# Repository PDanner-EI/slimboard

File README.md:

# Slimboard
Slim profile, split keyboard. Inspired by Corne(https://github.com/foostan/crkbd).

## Features:
- Split keyboard
- Slim profile for easy portability
- Bluetooth connectivity
- Key Layout fitted to own hand

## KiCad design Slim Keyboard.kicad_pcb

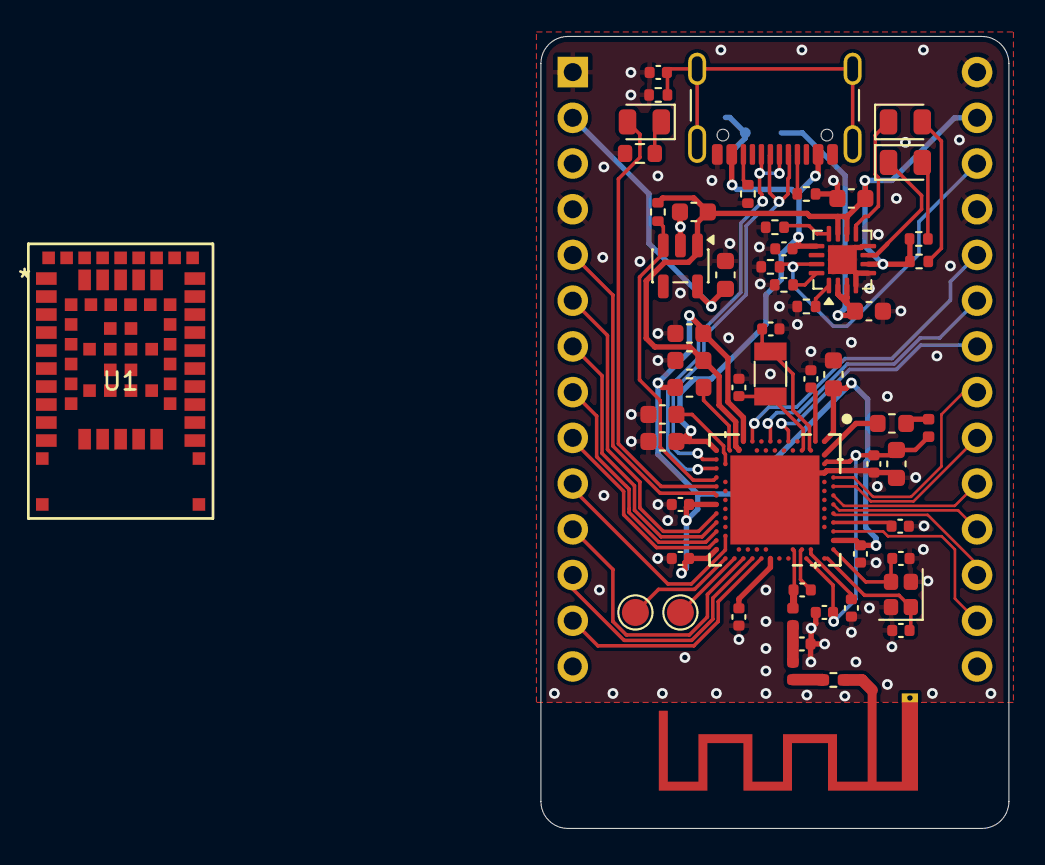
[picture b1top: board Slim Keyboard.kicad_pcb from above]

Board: 2 copper layers, 26.0 x 44.0 mm, 59 parts (1 on the bottom side), 61 nets.

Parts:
AE1: Antenna_Shield; 2.4GHz F Antenna
C1, C2, C6, C18: 100nF; C_0402_1005Metric
C3, C4, C11, C12: 12pF; C_0402_1005Metric
C5, C19, C20, C21, C23, C24, C25: 4.7uF; C_0603_1608Metric
C7, C8: 1uF; C_0603_1608Metric
C9: 47nF; C_0402_1005Metric
C10, C14: N.C.; C_0402_1005Metric
C13: 100pF; C_0402_1005Metric
C15: 1pF; C_0402_1005Metric
C16: 1.2pF; C_0402_1005Metric
C17: 820pF; C_0402_1005Metric
C22: 1uF; C_0402_1005Metric
C26: 10uF; C_0603_1608Metric
C27: 4.7nF; C_0402_1005Metric
D1: LTST-C170KFKT; LED_0805_2012Metric
D2: LTST-C170KGKT; LED_0805_2012Metric
D3: IN-S85AT5B; LED_0805_2012Metric
J1: USB_C_Receptacle_USB2.0_16P; USB_C_Receptacle_GCT_USB4105-xx-A_16P_TopMnt_Horizontal
J2: SWD; TestPoint_Pad_D1.5mm
J3: SWC; TestPoint_Pad_D1.5mm
J5: S2B-PH-SM4-TB; JST_S2B-PH-SM4-TB
J7: NRF52840_module
L1, L5: 10uH; L_0603_1608Metric
L2: 15nH; L_0402_1005Metric
L3: 4.7nH; L_0402_1005Metric
L4: 2.2nH; L_0402_1005Metric
R1: 0R; R_0402_1005Metric_Pad0.72x0.64mm_HandSolder
R2, R12: 1M; R_0402_1005Metric
R3: 10k; R_0402_1005Metric
R4, R5: 1k; R_0402_1005Metric
R6: 10M; R_0402_1005Metric
R7, R8: 5.1k; R_0402_1005Metric
R9: 1k; R_0603_1608Metric
R10: 3.1k; R_0402_1005Metric
R11: 3.6k; R_0402_1005Metric
U1: NINA-B306-00B; NINA-B3x6_UBL
U1#2: NRF52840-QIAA-R; AQFN73_7X7_NOR
U2: BQ24075RGT; VQFN-16-1EP_3x3mm_P0.5mm_EP1.6x1.6mm
U3: XC6220B331MR; SOT-23-5
Y1: ECS-.327-9-34B-TR; Crystal_SMD_3215-2Pin_3.2x1.5mm
Y2: XRCGB32M000F1S2KR0; Crystal_SMD_2016-4Pin_2.0x1.6mm

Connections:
BLED: D3.2 (A), U1.44 (GPIO_44), U1#2.AD10 (P0.15)
D0: J7.3 (D0_P0.08), U1.1 (GPIO_1)
D1: J7.2 (D1_P0.06), U1.2 (GPIO_2)
D2: J7.6 (D2_P0.17), U1.3 (GPIO_3)
D3: J7.7 (D3_P0.20), U1.4 (GPIO_4)
D4: J7.8 (D4_P0.22), U1.5 (GPIO_5)
D5: J7.9 (D5_P0.24), U1.7 (GPIO_7)
D6: J7.10 (D6_P1.00), U1.16 (GPIO_16)
D7: J7.11 (D7_P0.11), U1.17 (GPIO_17)
D8: J7.12 (D8_P1.04), U1.18 (GPIO_18)
D9: J7.13 (D9_P1.06), U1.20 (GPIO_20)
D11: J7.14 (D11_P0.09), U1.21 (GPIO_21)
D14: J7.16 (D14_P1.11), U1.22 (GPIO_22)
D15: J7.17 (D15_P1.13), U1.23 (GPIO_23)
D16: J7.15 (D16_P0.10), U1.24 (GPIO_24)
D18: J7.18 (D18_P1.15), U1.25 (GPIO_25)
D19: J7.19 (D19_P0.02), U1.27 (GPIO_27)
D20: J7.20 (D20_P0.29), U1.34 (GPIO_34)
D+: J1.A6 (D+), J1.B6 (D+), U1.54 (USBG_DP), U1#2.AD6 (D+)
D-: J1.A7 (D-), J1.B7 (D-), U1.55 (USBG_DM), U1#2.AD4 (D-)
EXT_VCC: C25.1, U3.5 (VOUT)
GND: AE1.2 (Shield), C1.2, C2.2, C3.2, C4.2, C5.2, C6.1, C7.1, C8.1, C9.1, C10.2, C11.2, C12.2, C13.1, C14.1, C15.1, C16.1, C17.2, C18.1, C19.2, C20.2, C21.2, C22.1, C23.2, C24.2, C25.2, C26.1, C27.1, J1.A1 (GND), J1.A12 (GND), J1.B1 (GND), J1.B12 (GND), J5.2, J7.1 (GND), J7.4 (GND), J7.5 (GND), J7.24 (GND), R2.2, R3.2, R7.2, R8.2, R9.2, R10.2, R11.2, R12.1, U1.6 (GND), U1.12 (GND), U1.14 (GND), U1.26 (GND), U1.30 (GND), U1.53 (GND), U1.EAGP1 (GND), U1.EAGP2 (GND), U1.EAGP3 (GND), U1.EAGP4 (GND), U1.EGP1 (GND), U1.EGP2 (GND), U1.EGP3 (GND), U1.EGP4 (GND), U1.EGP5 (GND), U1.EGP6 (GND), U1.EGP7 (GND), U1.EGP8 (GND), U1.EGP9 (GND), U1.EGP10 (GND), U1.EGP11 (GND), U1.EGP12 (GND), U1#2.74 (VSS), U1#2.B7 (VSS), U1#2.F23 (VSS_PA), U2.4 (~CE), U2.5 (EN2), U2.8 (VSS), U2.17 (VSS), U3.2 (GND), Y2.2, Y2.4
unnamed: AE1.1 (A), R1.2
unnamed: C16.2, L3.2, L4.1
unnamed: D1.2 (A), R4.1
unnamed: D1.1 (K), U2.9 (~CHG)
unnamed: D2.2 (A), R5.1
unnamed: D2.1 (K), U2.7 (~PGOOD)
unnamed: D3.1 (K), R9.1
unnamed: J1.A5 (CC1), R7.1
unnamed: J1.B5 (CC2), R8.1
unnamed: C27.2, J1.S1 (SHIELD), R12.2
unnamed: L1.2, L2.1
unnamed: L4.2, R1.1
unnamed: C15.2, L3.1, U1#2.H23 (ANT)
unnamed: L1.1, U1#2.B3 (DCC)
unnamed: L5.1, U1#2.AB2 (DCCH)
unnamed: C2.1, U1#2.C1 (DEC1)
unnamed: C10.1, U1#2.A18 (DEC2)
unnamed: C13.2, U1#2.D23 (DEC3)
unnamed: C8.2, C9.2, C14.2, L2.2, U1#2.B5 (DEC4), U1#2.E24 (DEC6)
unnamed: C17.1, U1#2.N24 (DEC5)
unnamed: C5.1, U1#2.AC5 (DECUSB)
unnamed: C3.1, U1#2.D2 (P0.00/XL1), Y1.2
unnamed: C4.1, U1#2.F2 (P0.01/XL2), Y1.1
unnamed: C12.1, U1#2.B24 (XC1), Y2.1
unnamed: C11.1, U1#2.A23 (XC2), Y2.3
unnamed: R10.1, U2.12 (ILIM)
unnamed: R11.1, U2.16 (ISET)
unnamed: R3.1, U2.1 (TS)
POWER_PIN: R6.1, U1#2.AD8 (P0.13), U3.3 (CE)
RESET: J7.23 (RESET), U1.19 (RESET_N)
SWC: J3.1, U1.11 (SWDCLK), U1#2.AA24 (SWDCLK)
SWD: J2.1, U1.15 (SWDIO), U1#2.AC24 (SWDIO)
SYSOFF_SWITCH: J7.21 (D21_P0.31), R2.1, U2.15 (SYSOFF)
VBAT: C24.1, J5.1, U2.2 (BAT), U2.3 (BAT)
VBUS: C19.1, C22.2, J1.A4 (VBUS), J1.A9 (VBUS), J1.B4 (VBUS), J1.B9 (VBUS), U1.31 (VBUS), U1#2.AD2 (VBUS), U2.13 (IN)
VDD: U1.9 (VCC_IO), U1.10 (VCC)
VDDH: C20.1, C23.1, C26.2, R4.2, R5.2, R6.2, U1#2.Y2 (VDDH), U2.6 (EN1), U2.10 (OUT), U2.11 (OUT), U3.1 (VIN)
VDD_NRF: C1.1, C6.2, C7.2, C18.2, C21.1, L5.2, U1#2.A22 (VDD), U1#2.AD14 (VDD), U1#2.AD23 (VDD), U1#2.B1 (VDD), U1#2.W1 (VDD)
_GPIO: U1.35 (GPIO_35), U1.36 (GPIO_36), U1.37 (GPIO_37), U1.38 (GPIO_38), U1.39 (GPIO_39), U1.40 (GPIO_40), U1.41 (GPIO_41), U1.42 (GPIO_42), U1.43 (GPIO_43)

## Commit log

2026-02-20 Enhance README with features and link
    Added features section and improved project description.
2026-02-20 Initial commit; MCU designed after manufacturer specs
2026-02-20 Replaced 32MHz Crystal with 3-pin for added shielding
2026-02-20 Removed floating GND symbol
2026-02-20 Added 0 Ohm resistor before antenna for later VNA tuning
2026-02-20 Added proper Labels
2026-02-20 Added charging schematic
2026-02-20 Added external VCC schematic
2026-02-20 Added USB connection
2026-02-21 Update footprints
2026-02-21 Added ISET and JST to Battery
2026-02-21 Updated Footprints
2026-02-21 Added PCB Test Layout
2026-02-21 Adjusted PCB Test Layout
2026-02-25 Added test Antenna
2026-02-25 Added actual JST connector
2026-02-26 Adjusted Footprint sizes
2026-02-27 Started PCB design
2026-03-09 Changed Pinout
2026-03-09 Changed Module Pinout
2026-03-09 Connected GPIO
2026-03-09 Placed Components and started routing
2026-03-10 Routing
2026-03-10 Routing Done; DFM problems to solve
2026-03-14 DFM problems to solve; CE compliance issue
2026-03-15 Replaced IC with NINA Module
